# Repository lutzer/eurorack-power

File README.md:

# Eurorack Power Supplies

schematics for eurorack power supplies

## Setup

* copy libraries from *schematics/libraries* to eagle libraries folder
* copy schematics to eagle project folder
* open project
* activate libraries with right click and *use* in library manager

## Notes

* To avoid oscillation problems when using DKMW30f-12:
  * Replace R6 with wired connection
  * Don't solder in C3

## BOM

### DC DC Converter Options

#### 12V

* 30W: https://www.mouser.de/ProductDetail/MEAN-WELL/DKMW30F-12/?qs=%2Fha2pyFadugPfVRQAxI4Iwf31KvWSSQ5yO6OlzoqYdGM367f8%2FWl4w%3D%3D
* 15W: https://www.mouser.de/ProductDetail/MEAN-WELL/DKMW15F-12/?qs=%2Fha2pyFaduiYoYgxwNsfdZ5VubX0%252Bab1un6BH80socxHllnzIFJ%2FvQ%3D%3D

#### 5V

* 1A: https://www.reichelt.de/dc-dc-wandler-tsr-1-1-w-5-v-1000-ma-sil-to-220-tsr-1-2450-p116850.html?search=tsr+1-2450

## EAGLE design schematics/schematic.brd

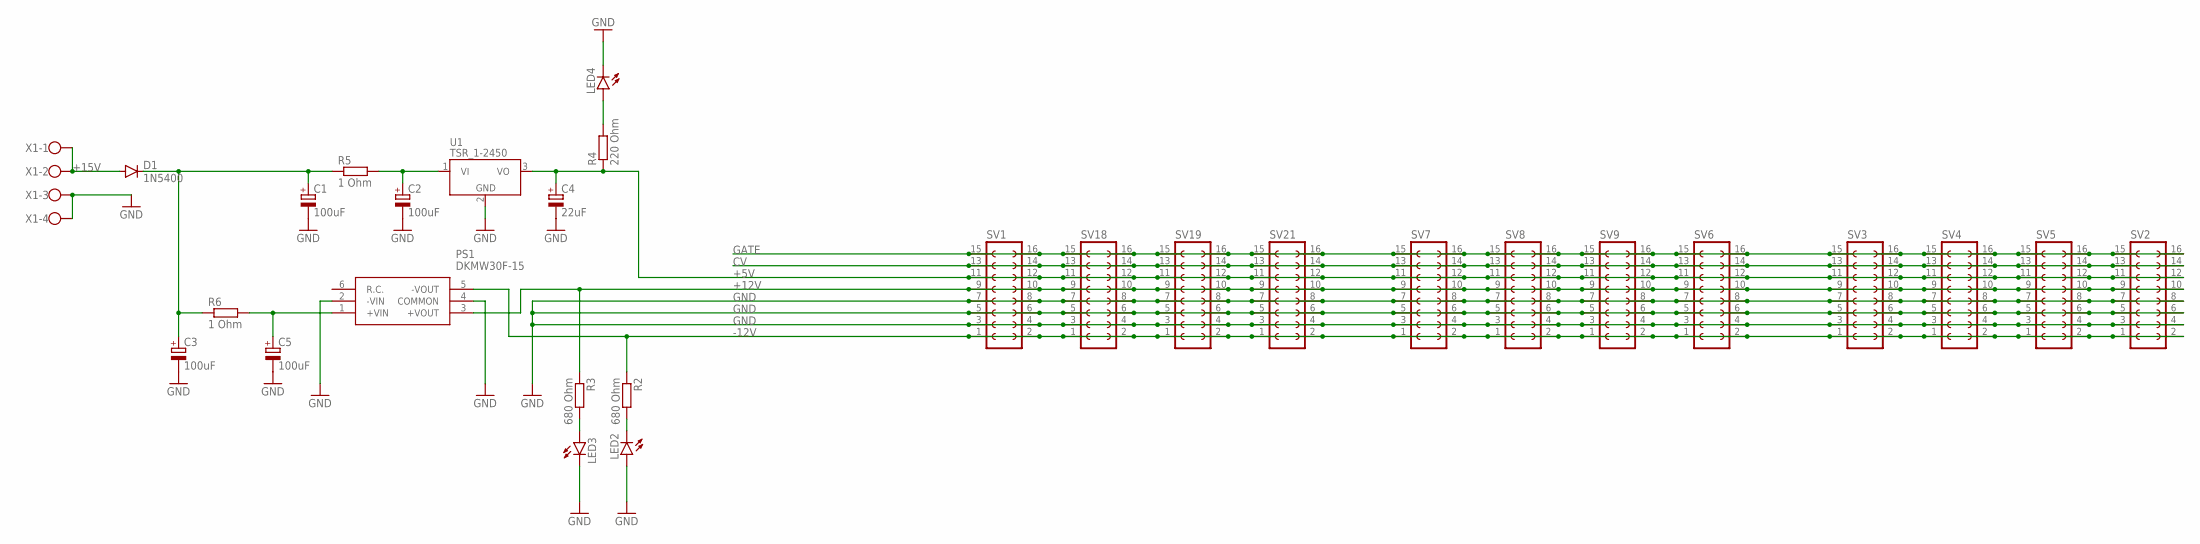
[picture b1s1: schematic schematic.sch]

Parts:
C1, C2, C3, C5: 100uF; E3,5-8
C4: 22uF; E2,5-5
D1: 1N5400; DO201-15
LED2, LED3, LED4: LED3MM
PS1: DKMW30F-15; DKMW30F15
R2, R3: 680 Ohm; 0207/10
R4: 220 Ohm; 0207/10
R5, R6: 1 Ohm; 0207/10
SV1, SV2, SV3, SV4, SV5, SV6, SV7, SV8, SV9, SV18, SV19, SV21: FE08-2
U1: TSR_1-2450; TSR-1
X1: W237-4

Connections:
+5V: C4.+, R4.1, SV1.11, SV1.12, SV2.11, SV2.12, SV3.11, SV3.12, SV4.11, SV4.12, SV5.11, SV5.12, SV6.11, SV6.12, SV7.11, SV7.12, SV8.11, SV8.12, SV9.11, SV9.12, SV18.11, SV18.12, SV19.11, SV19.12, SV21.11, SV21.12, U1.3 (VO)
+12V: PS1.3 (+VOUT), R3.1, SV1.9, SV1.10, SV2.9, SV2.10, SV3.9, SV3.10, SV4.9, SV4.10, SV5.9, SV5.10, SV6.9, SV6.10, SV7.9, SV7.10, SV8.9, SV8.10, SV9.9, SV9.10, SV18.9, SV18.10, SV19.9, SV19.10, SV21.9, SV21.10
+15V: D1.A, X1.1, X1.2
-12V: PS1.5 (-VOUT), R2.1, SV1.1, SV1.2, SV2.1, SV2.2, SV3.1, SV3.2, SV4.1, SV4.2, SV5.1, SV5.2, SV6.1, SV6.2, SV7.1, SV7.2, SV8.1, SV8.2, SV9.1, SV9.2, SV18.1, SV18.2, SV19.1, SV19.2, SV21.1, SV21.2
CV: SV1.13, SV1.14, SV2.13, SV2.14, SV3.13, SV3.14, SV4.13, SV4.14, SV5.13, SV5.14, SV6.13, SV6.14, SV7.13, SV7.14, SV8.13, SV8.14, SV9.13, SV9.14, SV18.13, SV18.14, SV19.13, SV19.14, SV21.13, SV21.14
GATE: SV1.15, SV1.16, SV2.15, SV2.16, SV3.15, SV3.16, SV4.15, SV4.16, SV5.15, SV5.16, SV6.15, SV6.16, SV7.15, SV7.16, SV8.15, SV8.16, SV9.15, SV9.16, SV18.15, SV18.16, SV19.15, SV19.16, SV21.15, SV21.16
GND: C1.-, C2.-, C3.-, C4.-, C5.-, LED2.A, LED3.K (C), LED4.K (C), PS1.2 (-VIN), PS1.4 (COMMON), SV1.3, SV1.4, SV1.5, SV1.6, SV1.7, SV1.8, SV2.3, SV2.4, SV2.5, SV2.6, SV2.7, SV2.8, SV3.3, SV3.4, SV3.5, SV3.6, SV3.7, SV3.8, SV4.3, SV4.4, SV4.5, SV4.6, SV4.7, SV4.8, SV5.3, SV5.4, SV5.5, SV5.6, SV5.7, SV5.8, SV6.3, SV6.4, SV6.5, SV6.6, SV6.7, SV6.8, SV7.3, SV7.4, SV7.5, SV7.6, SV7.7, SV7.8, SV8.3, SV8.4, SV8.5, SV8.6, SV8.7, SV8.8, SV9.3, SV9.4, SV9.5, SV9.6, SV9.7, SV9.8, SV18.3, SV18.4, SV18.5, SV18.6, SV18.7, SV18.8, SV19.3, SV19.4, SV19.5, SV19.6, SV19.7, SV19.8, SV21.3, SV21.4, SV21.5, SV21.6, SV21.7, SV21.8, U1.2 (GND), X1.3, X1.4
unnamed: LED2.K (C), R2.2
unnamed: LED3.A, R3.2
unnamed: LED4.A, R4.2
unnamed: C1.+, C3.+, D1.C, R5.1, R6.1
VI: C2.+, R5.2, U1.1 (VI)
VI1: C5.+, PS1.1 (+VIN), R6.2

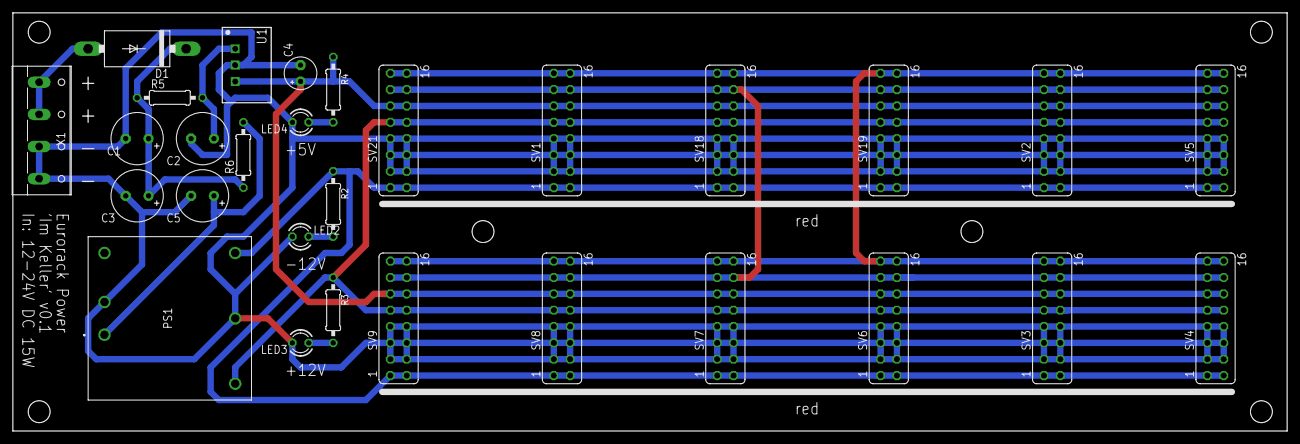
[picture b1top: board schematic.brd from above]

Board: 2 copper layers, 198.1 x 65.0 mm, 29 parts (0 on the bottom side), 13 nets.

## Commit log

2021-02-09 added schematic
2021-02-09 added gitignore
2021-02-14 added eagle copy script
2021-02-15 changed schematic
2021-02-15 fixed power header connections
2021-02-16 added first board layout
2021-02-16 added drillholes and descriptions
2021-02-17 added double input screw terminals
2021-02-17 removed airwire errors
2021-02-17 added stripe mark
2021-02-17 replaced dc dc converter with smaller 15W version
2021-02-18 removed airwires, added dkmw30f lib
2021-02-18 added 2 crc groups
2021-02-19 bugfixes
2021-02-19 changed distance of power headers
2021-02-20 fixed wire clearance
2021-11-09 added 4 more headers to board
2021-11-09 some minor fixes on schematic
